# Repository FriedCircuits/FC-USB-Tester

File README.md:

FC-USB-Tester
================
Code and design files for the USB Tester

Hardware available on [https://www.tindie.com/stores/FriedCircuits/](https://www.tindie.com/stores/FriedCircuits/)

More info can be found on [http://friedcircuits.us/docs/usb-tester](http://friedcircuits.us/docs/usb-tester)

License: All source code and designs are released under 

Creative Commons NonCommercial-ShareAlike 

CC BY-NC-SA

Please contact me for commercial opportunities.

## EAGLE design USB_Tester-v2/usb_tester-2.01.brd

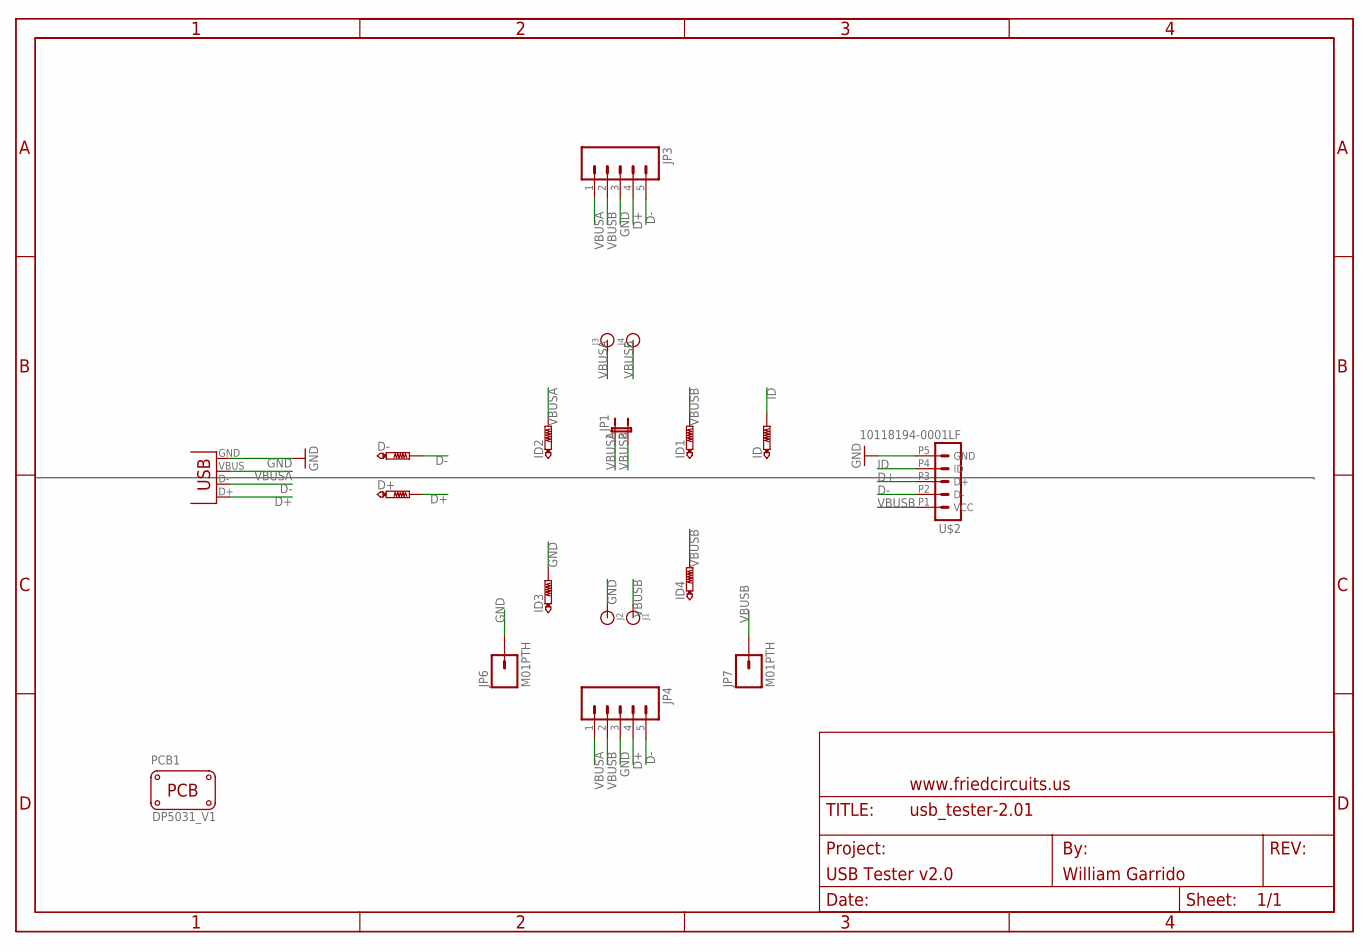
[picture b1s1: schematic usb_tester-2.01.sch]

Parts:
D+: PTR1PAD1-20; P1-20
D-: PTR1PAD1-20; P1-20
ID, ID1, ID2, ID3, ID4: PTR1PAD1-20; P1-20
J1, J2, J3, J4: BANANA_CONN
JP1: JUMPER-2PTH_LOCK; 1X02_LOCK
JP3, JP4: M05LOCK; 1X05_LOCK
JP6, JP7: M01PTH; 1X01
PCB1: PCB_DP_RECTANGLE-31X50; DP5031_V1
U$1: FRAME_DINA4_L; FC_CREDIT
U$2: 10118194-0001LF
USB-DEVICE: USB-A-SMD; USB-A-S-NOSILK-FEMALE

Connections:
D+: D+.TP, JP3.4, JP4.4, U$2.P3 (D+), USB-DEVICE.D+
D-: D-.TP, JP3.5, JP4.5, U$2.P2 (D-), USB-DEVICE.D-
GND: ID3.TP, J2.P$1, JP3.3, JP4.3, JP6.1, U$2.P5 (GND), USB-DEVICE.GND
ID: ID.TP, U$2.P4 (ID)
VBUSA: ID2.TP, J3.P$1, JP1.1, JP3.1, JP4.1, USB-DEVICE.VBUS
VBUSB: ID1.TP, ID4.TP, J1.P$1, J4.P$1, JP1.2, JP3.2, JP4.2, JP7.1, U$2.P1 (VCC)

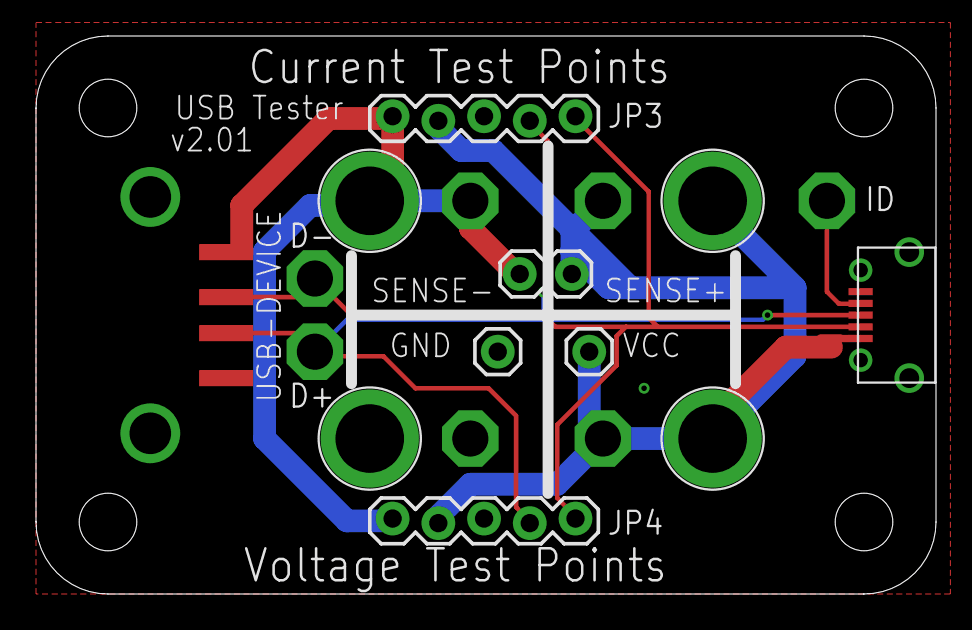
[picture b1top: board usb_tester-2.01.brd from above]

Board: 2 copper layers, 50.0 x 31.0 mm, 20 parts (0 on the bottom side), 6 nets.

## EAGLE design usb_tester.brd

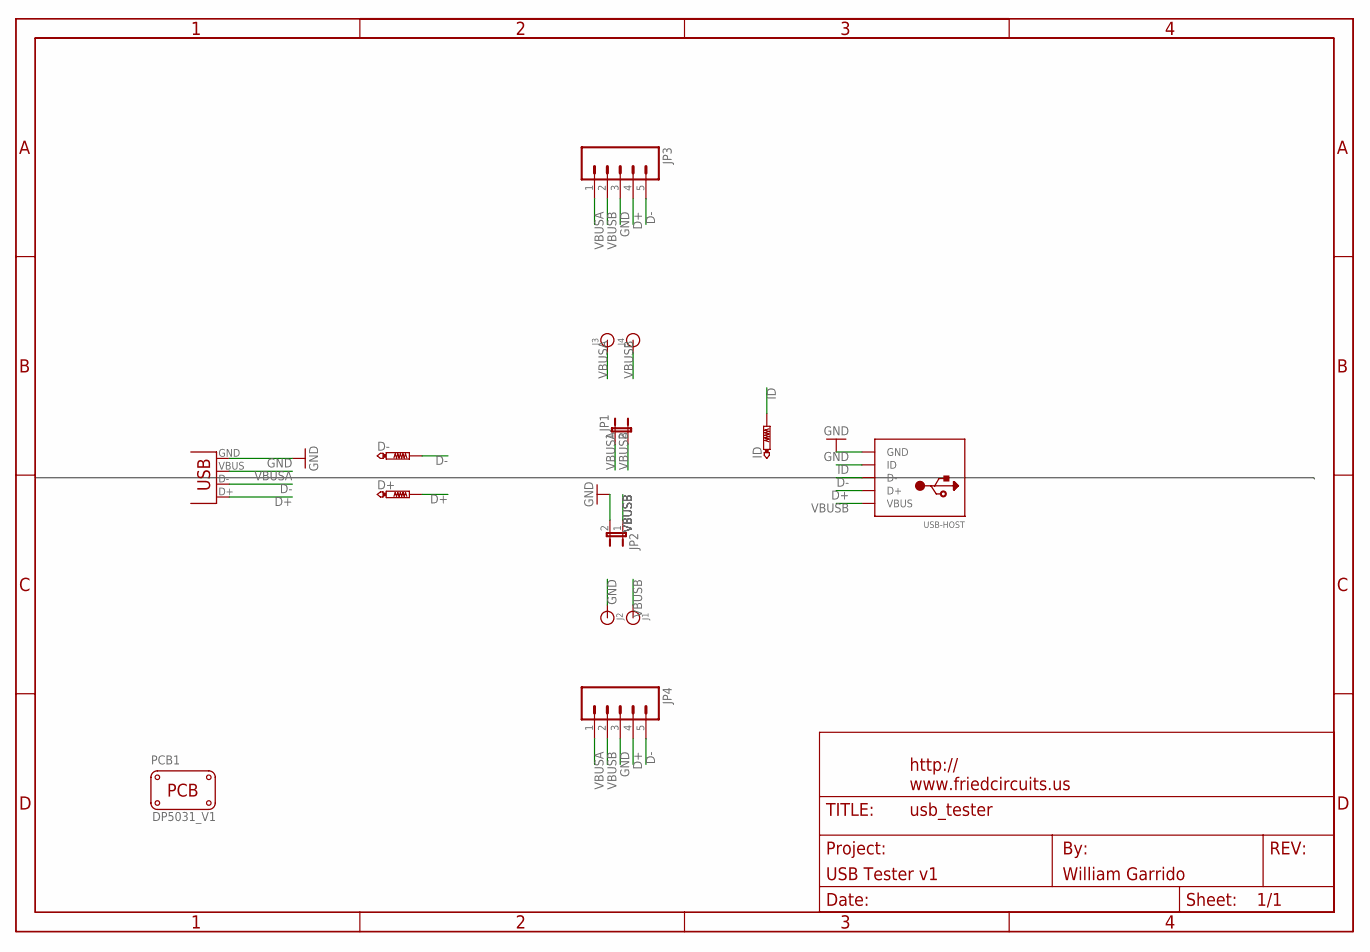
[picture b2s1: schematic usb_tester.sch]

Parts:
D+: PTR1PAD1-20; P1-20
D-: PTR1PAD1-20; P1-20
ID: PTR1PAD1-20; P1-20
J1, J2, J3, J4: BANANA_CONN
JP1, JP2: JUMPER-2PTH_LOCK; 1X02_LOCK
JP3, JP4: M05LOCK; 1X05_LOCK
PCB1: PCB_DP_RECTANGLE-31X50; DP5031_V1
U$1: FRAME_DINA4_L; FC_CREDIT
USB-DEVICE: USB-A-SMD; USB-A-S-NOSILK-FEMALE
USB-HOST: USBMINIB; USB-MINIB

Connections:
D+: D+.TP, JP3.4, JP4.4, USB-DEVICE.D+, USB-HOST.D+
D-: D-.TP, JP3.5, JP4.5, USB-DEVICE.D-, USB-HOST.D-
GND: J2.P$1, JP2.2, JP3.3, JP4.3, USB-DEVICE.GND, USB-HOST.GND
ID: ID.TP, USB-HOST.ID
VBUSA: J3.P$1, JP1.1, JP3.1, JP4.1, USB-DEVICE.VBUS
VBUSB: J1.P$1, J4.P$1, JP1.2, JP2.1, JP3.2, JP4.2, USB-HOST.VBUS

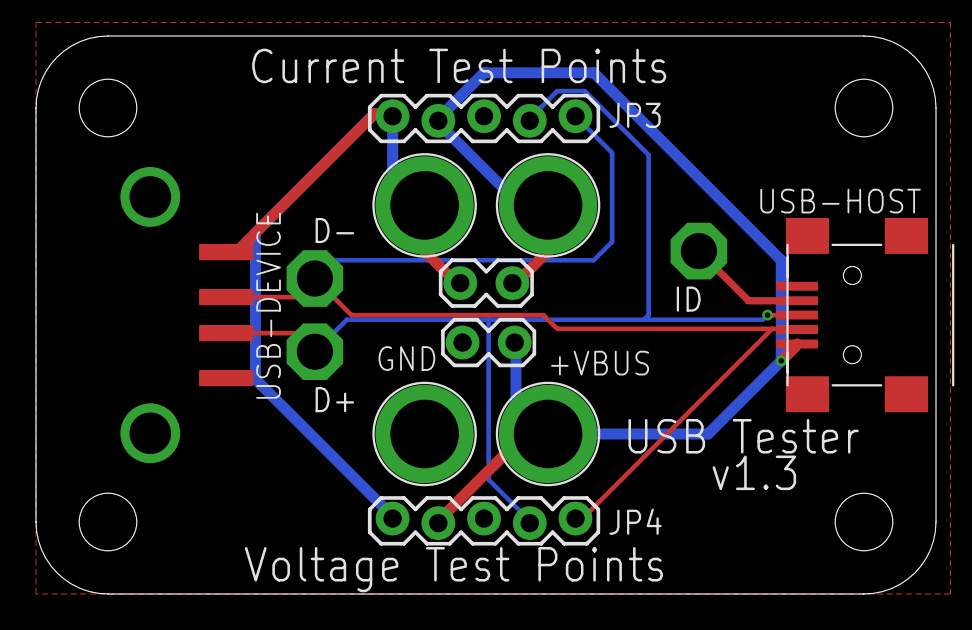
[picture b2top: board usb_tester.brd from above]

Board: 2 copper layers, 50.0 x 31.0 mm, 15 parts (0 on the bottom side), 6 nets.

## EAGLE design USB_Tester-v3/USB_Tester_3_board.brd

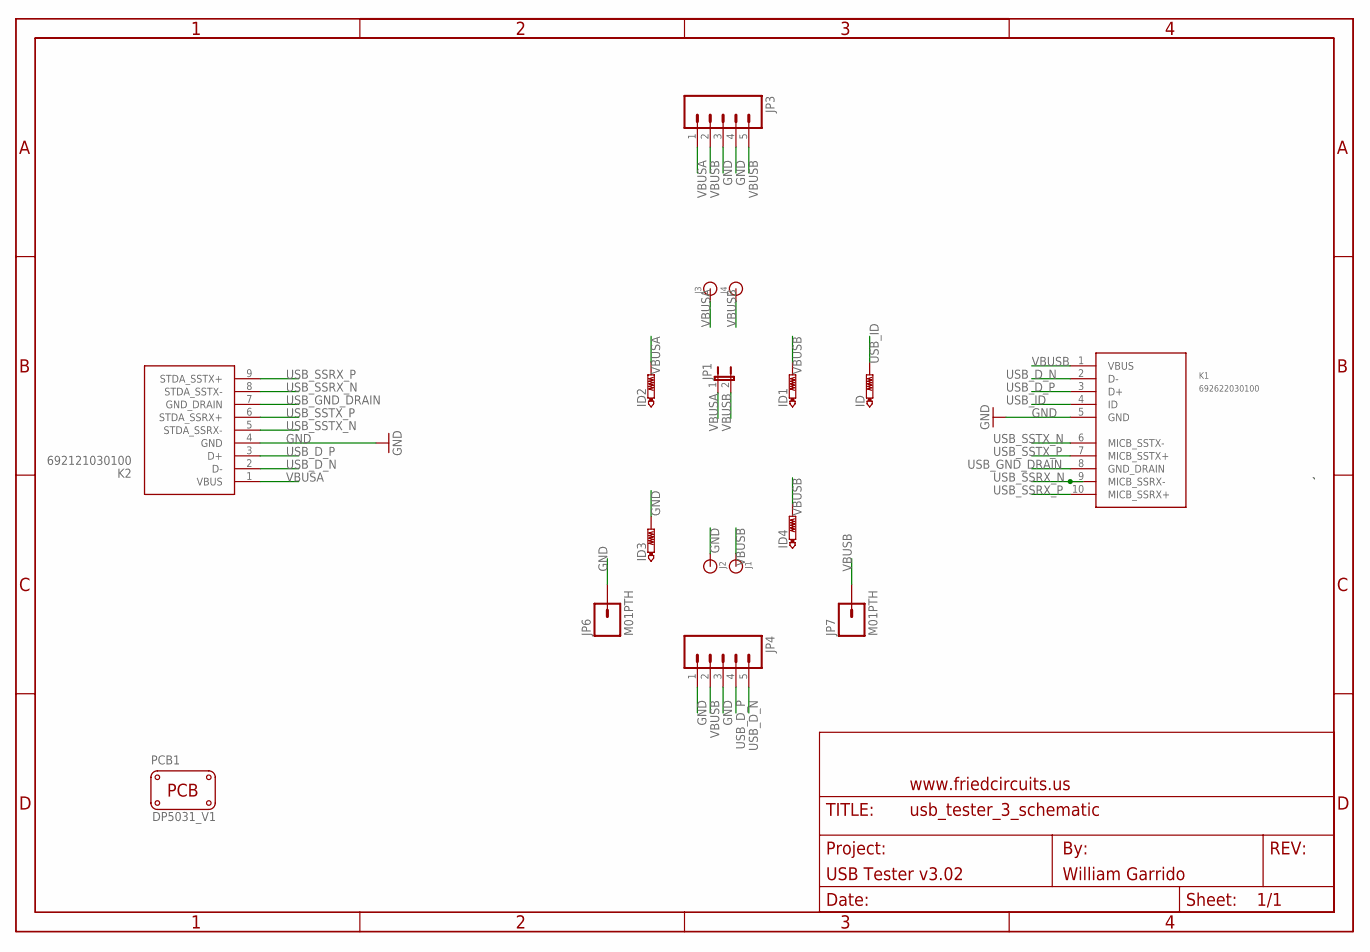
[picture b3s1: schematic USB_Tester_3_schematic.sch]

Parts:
ID, ID1, ID2, ID3, ID4: PTR1PAD1-20; P1-20
J1, J2, J3, J4: BANANA_CONN
JP1: JUMPER-2PTH_LOCK; 1X02_LOCK
JP3, JP4: M05LOCK; 1X05_LOCK
JP6, JP7: M01PTH; 1X01
K1: 692622030100
K2: 692121030100
PCB1: PCB_DP_RECTANGLE-31X50; DP5031_V1
U$1: FRAME_DINA4_L; FC_CREDIT

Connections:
GND: ID3.TP, J2.P$1, JP3.3, JP3.4, JP4.1, JP4.3, JP6.1, K1.5 (GND), K2.4 (GND)
USB_D_N: JP4.5, K1.2 (D-), K2.2 (D-)
USB_D_P: JP4.4, K1.3 (D+), K2.3 (D+)
USB_GND_DRAIN: K1.8 (GND_DRAIN), K2.7 (GND_DRAIN)
USB_ID: ID.TP, K1.4 (ID)
USB_SSRX_N: K1.9 (MICB_SSRX-), K2.8 (STDA_SSTX-)
USB_SSRX_P: K1.10 (MICB_SSRX+), K2.9 (STDA_SSTX+)
USB_SSTX_N: K1.6 (MICB_SSTX-), K2.5 (STDA_SSRX-)
USB_SSTX_P: K1.7 (MICB_SSTX+), K2.6 (STDA_SSRX+)
VBUSA: ID2.TP, J3.P$1, JP1.1, JP3.1, K2.1 (VBUS)
VBUSB: ID1.TP, ID4.TP, J1.P$1, J4.P$1, JP1.2, JP3.2, JP3.5, JP4.2, JP7.1, K1.1 (VBUS)

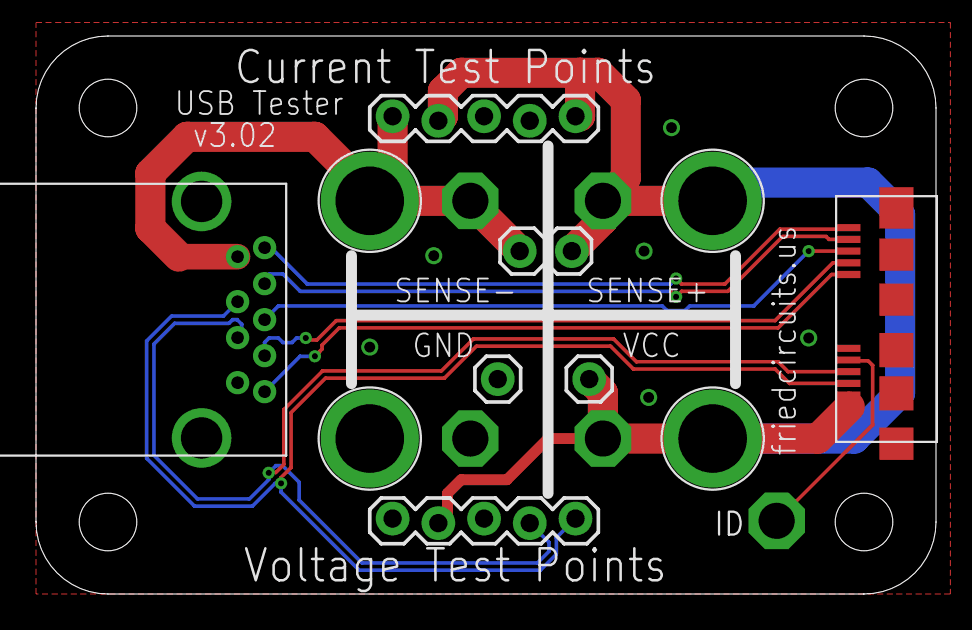
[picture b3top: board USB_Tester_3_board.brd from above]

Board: 2 copper layers, 50.0 x 31.0 mm, 18 parts (0 on the bottom side), 11 nets.

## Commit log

2013-01-30 Added schematic PNG
2013-01-30 Fixed over lapping symbol
2013-02-09 Changed USB A footprint
2013-03-13 Updated license
2013-04-23 Added design files in Eagle and PNG
2013-12-21 Setup to add version 2 files
2014-12-21 Added 2.0 Eagle and PNG
2018-02-19 Added USB Tester 3 design files

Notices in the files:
parts and their libraries:
SparkFun-Passives: Licensing: CC v3.0 Share-Alike You are welcome to use this library for commercial purposes.
Wuerth_Elektronik_eiCan_Communication_Co: Copyright: Würth Elektronik
